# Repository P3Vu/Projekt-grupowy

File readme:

Repozytorium powstało na potrzeby projektu grupowego (Edycja 2020/2021) prowadzonego jako jedne z wymagań na II stopniu studiów 
kierunku Elektronika i Telekomunikacja.

Tematem projektu opisanego w repozytorium jest Rozproszony System Inteligentnego Oświetlenia Ulicznego, którego celem jest
stworzenie systemu składającego się z lamp ulicznych dokonujących odpowiednich pomiarów oraz komunikujących się bezprzewodowo
(np. z wykorzystaniem interfejsu LoRaWAN) z serwerem celem sterowania oraz zarządzania.

Członkami zespołu są studenci katedry Metrologii i Optoelektroniki z specjalizacją uzupełniająca Systemy Wbudowane:

1. inż. Paweł Wojciechowski (Lider Zespołu)
2. inż. Luiza Błaszczak
3. inż. Anita Kaszuba

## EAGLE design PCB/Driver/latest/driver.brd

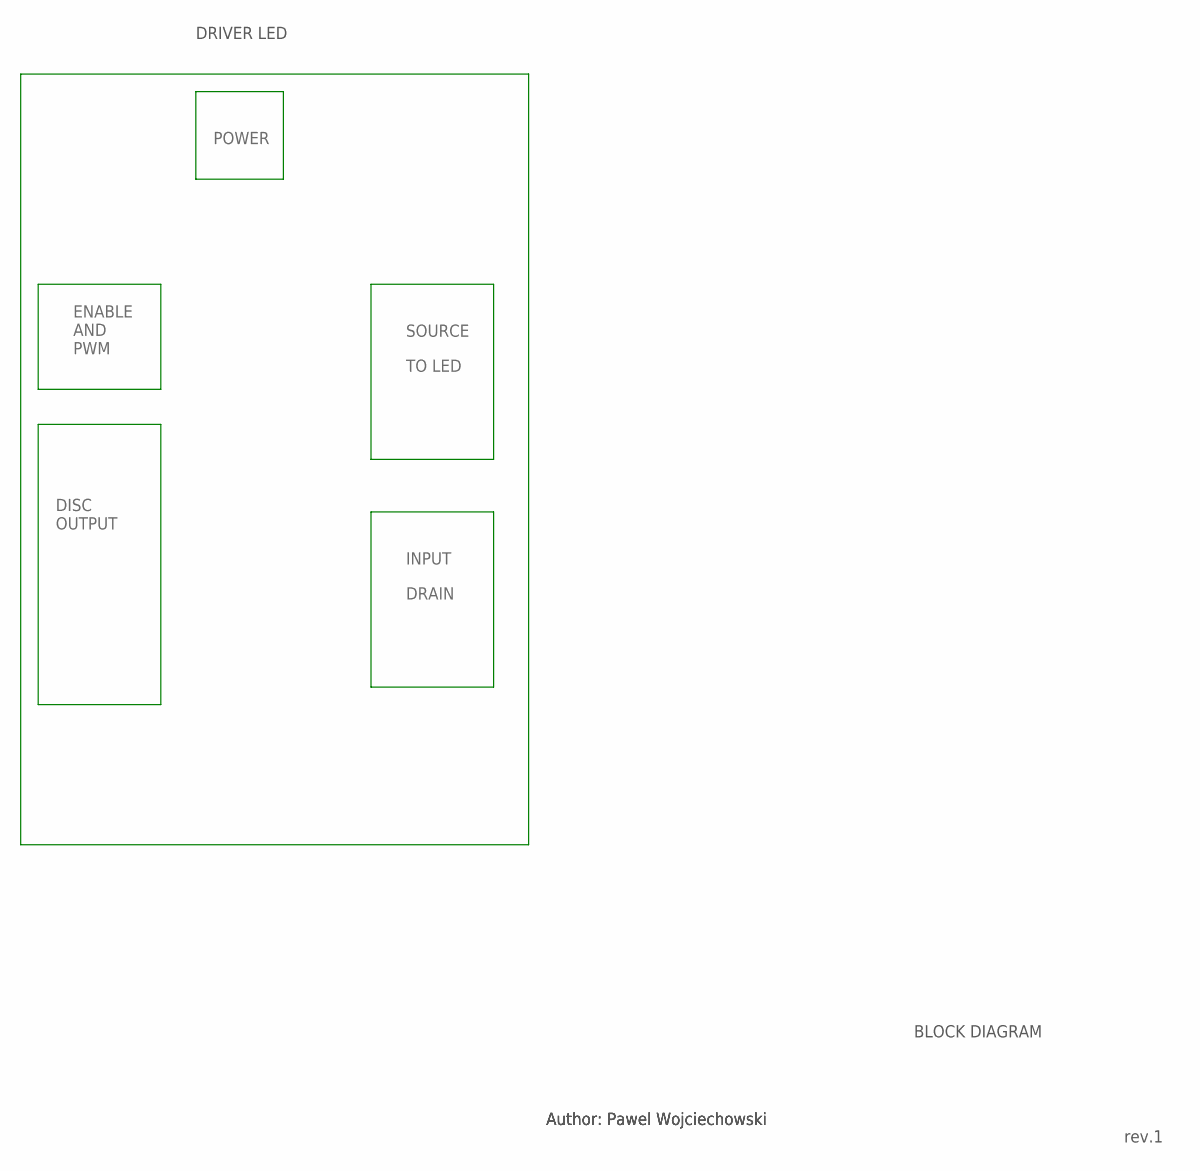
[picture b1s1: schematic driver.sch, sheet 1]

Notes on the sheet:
BLOCK DIAGRAM
Author: Pawel Wojciechowski
DRIVER LED
rev.1
ENABLE AND PWM
DISC OUTPUT
POWER
SOURCE
TO LED
INPUT
DRAIN

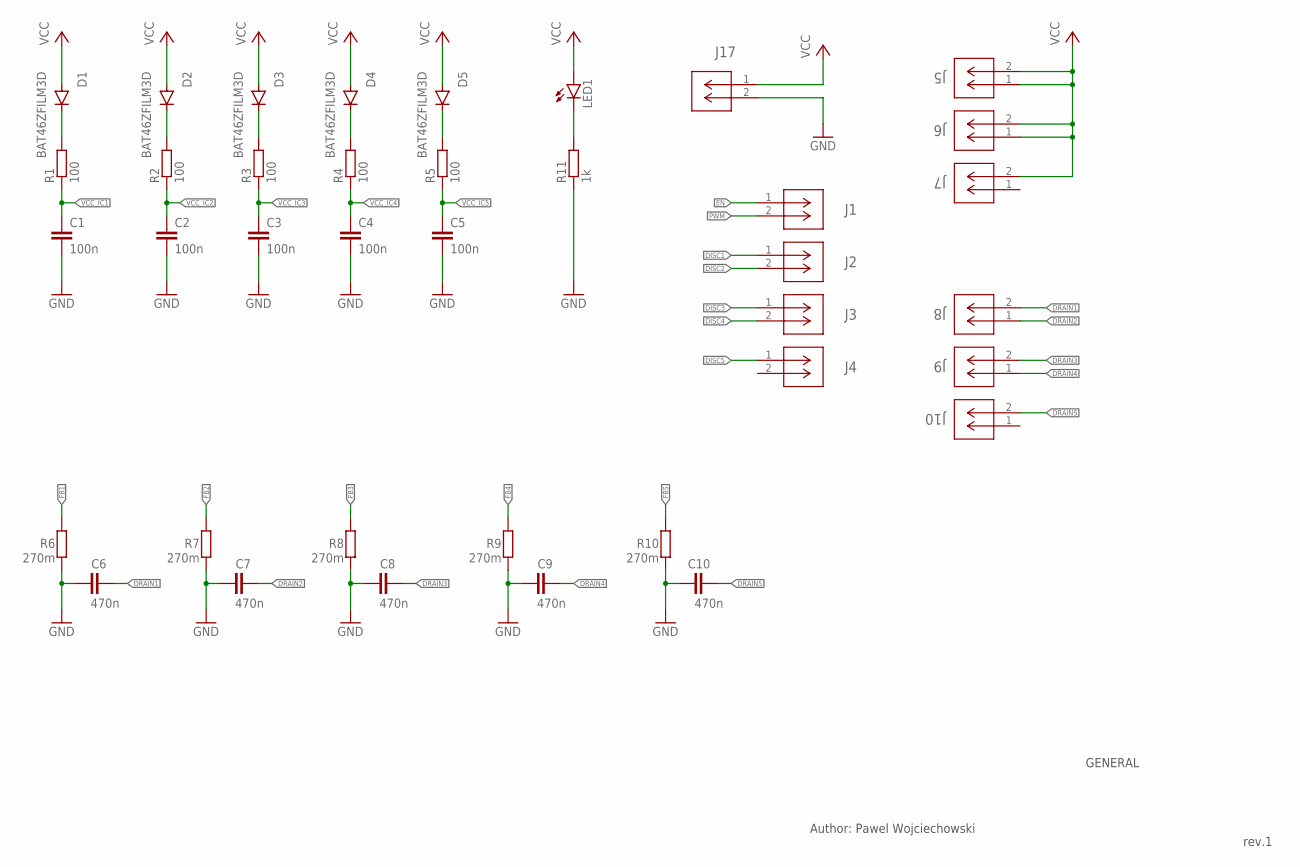
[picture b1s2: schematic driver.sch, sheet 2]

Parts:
C1, C2, C3, C4, C5: 100n; C0603
C6, C7, C8, C9, C10: 470n; C0805
D1, D2, D3, D4, D5: BAT46ZFILM3D; SOD-123
J1, J2, J3, J4, J5, J6, J7, J8, J9, J10, J17: 1776275-2; CONN2_1776275-2
LED1: LEDSMT1206; 1206
R1, R2, R3, R4, R5: 100; R0603
R6, R7, R8, R9, R10: 270m; R0603
R11: 1k; R0603

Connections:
DISC1: J2.1; also elsewhere on the board
DISC2: J2.2; also elsewhere on the board
DISC3: J3.1; also elsewhere on the board
DISC4: J3.2; also elsewhere on the board
DISC5: J4.1; also elsewhere on the board
DRAIN1: C6.2, J8.2; also elsewhere on the board
DRAIN2: C7.2, J8.1; also elsewhere on the board
DRAIN3: C8.2, J9.2; also elsewhere on the board
DRAIN4: C9.2, J9.1; also elsewhere on the board
DRAIN5: C10.2, J10.2; also elsewhere on the board
EN: J1.1; also elsewhere on the board
FB1: R6.2; also elsewhere on the board
FB2: R7.2; also elsewhere on the board
FB3: R8.2; also elsewhere on the board
FB4: R9.2; also elsewhere on the board
FB5: R10.2; also elsewhere on the board
GND: C1.2, C2.2, C3.2, C4.2, C5.2, C6.1, C7.1, C8.1, C9.1, C10.1, J17.2, R6.1, R7.1, R8.1, R9.1, R10.1, R11.1; also elsewhere on the board
unnamed: D1.C, R1.2
unnamed: D2.C, R2.2
unnamed: D3.C, R3.2
unnamed: D4.C, R4.2
unnamed: D5.C, R5.2
unnamed: LED1.C, R11.2
PWM: J1.2; also elsewhere on the board
VCC: D1.A, D2.A, D3.A, D4.A, D5.A, J5.1, J5.2, J6.1, J6.2, J7.2, J17.1, LED1.A
VCC_IC1: C1.1, R1.1; also elsewhere on the board
VCC_IC2: C2.1, R2.1; also elsewhere on the board
VCC_IC3: C3.1, R3.1; also elsewhere on the board
VCC_IC4: C4.1, R4.1; also elsewhere on the board
VCC_IC5: C5.1, R5.1; also elsewhere on the board

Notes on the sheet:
Author: Pawel Wojciechowski
rev.1
GENERAL

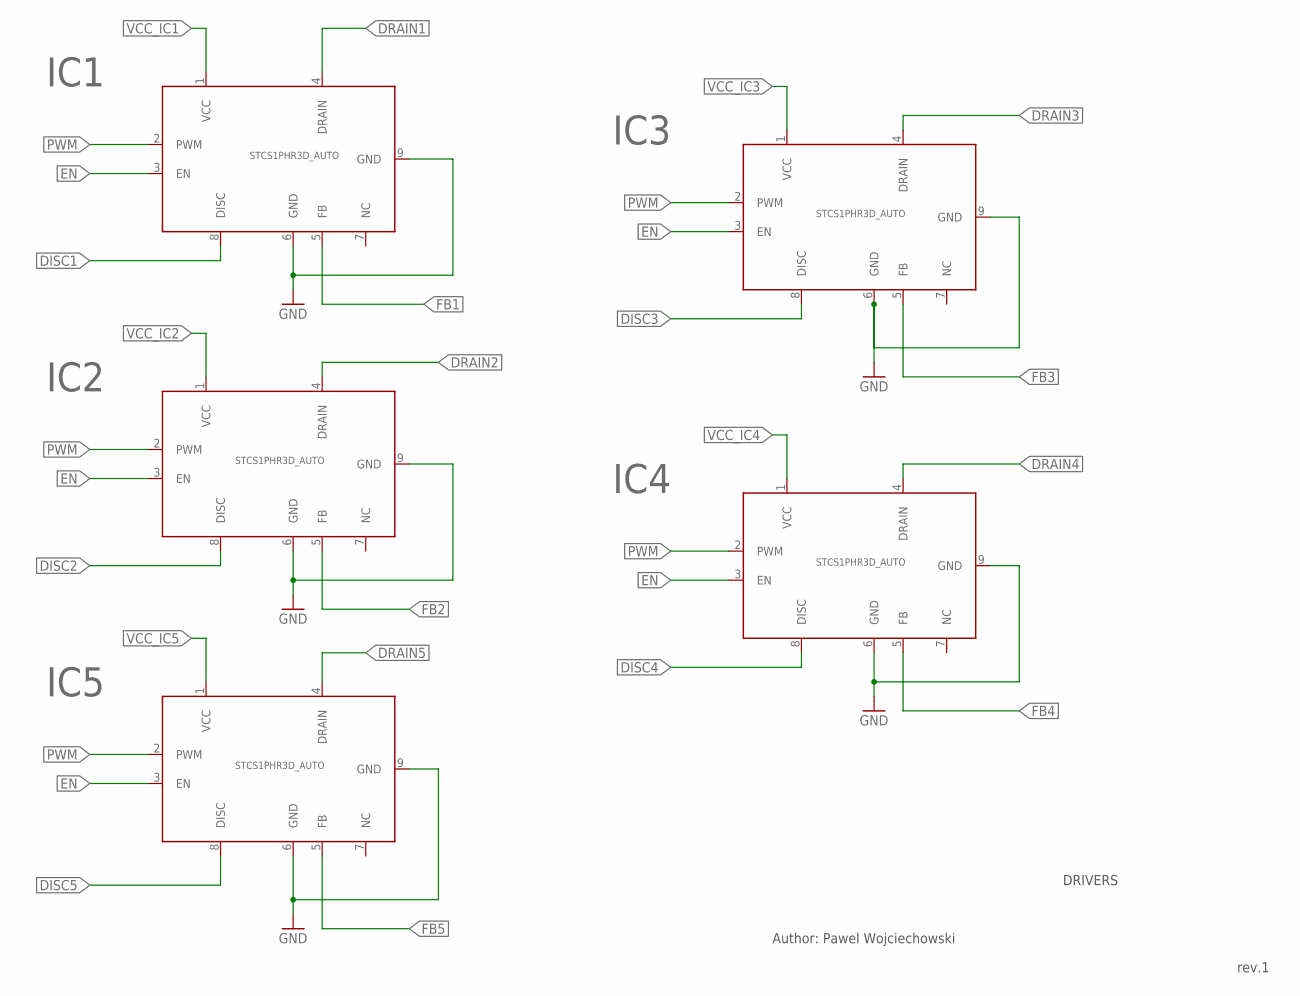
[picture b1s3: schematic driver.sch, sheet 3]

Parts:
IC1, IC2, IC3, IC4, IC5: STCS1PHR3D_AUTO; SOIC127P600X170-9T251X320N

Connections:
DISC1: IC1.8 (DISC); also elsewhere on the board
DISC2: IC2.8 (DISC); also elsewhere on the board
DISC3: IC3.8 (DISC); also elsewhere on the board
DISC4: IC4.8 (DISC); also elsewhere on the board
DISC5: IC5.8 (DISC); also elsewhere on the board
DRAIN1: IC1.4 (DRAIN); also elsewhere on the board
DRAIN2: IC2.4 (DRAIN); also elsewhere on the board
DRAIN3: IC3.4 (DRAIN); also elsewhere on the board
DRAIN4: IC4.4 (DRAIN); also elsewhere on the board
DRAIN5: IC5.4 (DRAIN); also elsewhere on the board
EN: IC1.3 (EN), IC2.3 (EN), IC3.3 (EN), IC4.3 (EN), IC5.3 (EN); also elsewhere on the board
FB1: IC1.5 (FB); also elsewhere on the board
FB2: IC2.5 (FB); also elsewhere on the board
FB3: IC3.5 (FB); also elsewhere on the board
FB4: IC4.5 (FB); also elsewhere on the board
FB5: IC5.5 (FB); also elsewhere on the board
GND: IC1.6 (GND), IC1.9 (GND), IC2.6 (GND), IC2.9 (GND), IC3.6 (GND), IC3.9 (GND), IC4.6 (GND), IC4.9 (GND), IC5.6 (GND), IC5.9 (GND); also elsewhere on the board
PWM: IC1.2 (PWM), IC2.2 (PWM), IC3.2 (PWM), IC4.2 (PWM), IC5.2 (PWM); also elsewhere on the board
VCC_IC1: IC1.1 (VCC); also elsewhere on the board
VCC_IC2: IC2.1 (VCC); also elsewhere on the board
VCC_IC3: IC3.1 (VCC); also elsewhere on the board
VCC_IC4: IC4.1 (VCC); also elsewhere on the board
VCC_IC5: IC5.1 (VCC); also elsewhere on the board

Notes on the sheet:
DRIVERS
Author: Pawel Wojciechowski
rev.1

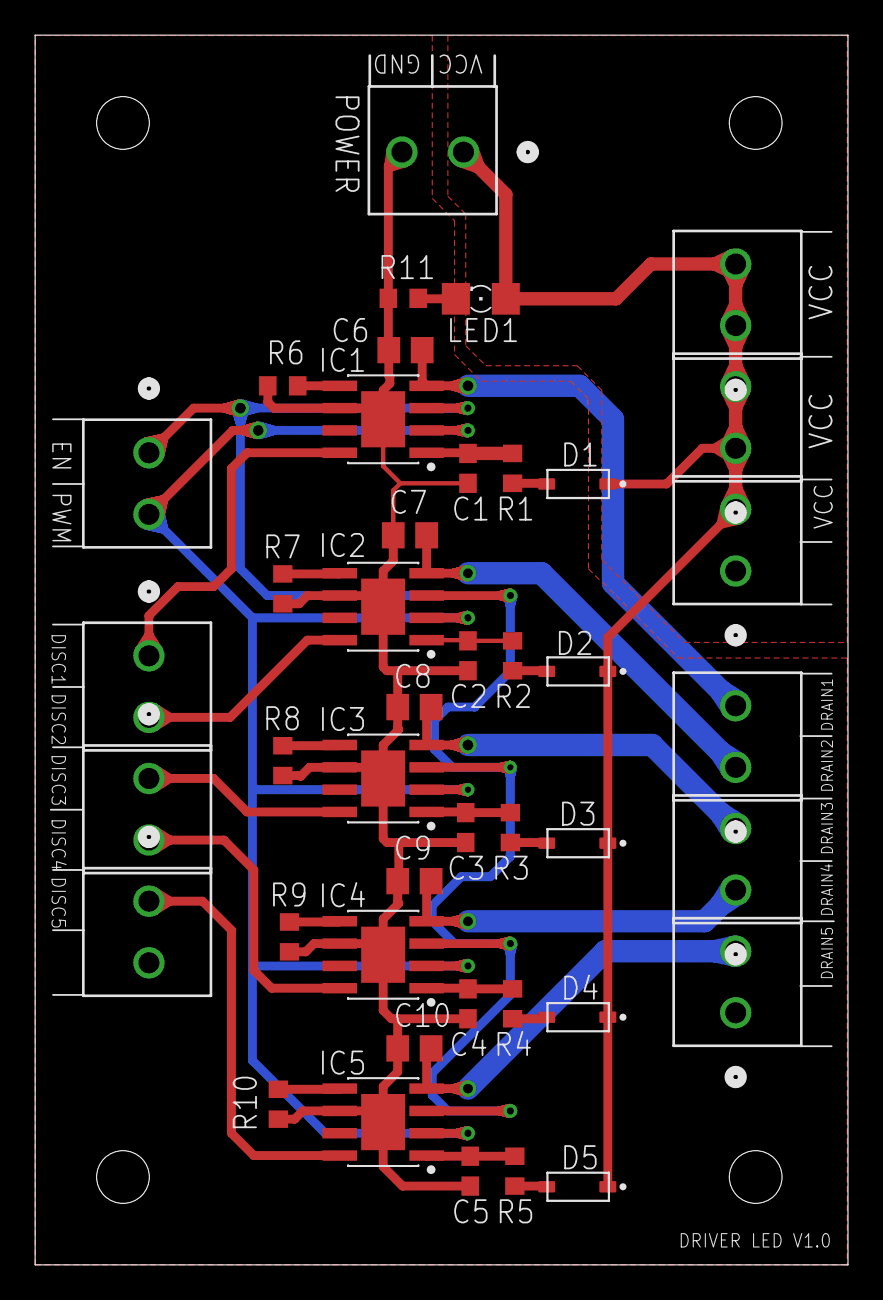
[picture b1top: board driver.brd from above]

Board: 2 copper layers, 46.3 x 70.0 mm, 43 parts (0 on the bottom side), 30 nets.

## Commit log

2020-04-09 Rename PMS.ioc to Czujnik Pylu/ PMS.ioc
    Przenosze do odpowiedniego folderu
2020-04-09 Rename Czujnik Pylu/ PMS.ioc to Czujnik pylu/PMS.ioc
2020-04-09 Rename Inc/main.h to Czujnik pylu/Inc/main.h
2020-04-09 Create Czujnik pylu
2020-05-04 Test dodawania test.c
2020-05-04 Usuwam test.c
2020-05-04 Dodaje pelny projekt z czujnikiem pylu PMS3003
2020-05-04 Usuwam poprzedni niepelny folder z czujnikiem pylu
2020-05-04 Projekt PCB
2020-05-07 Test
2020-05-08 Added Czujnik BME280
2020-05-08 Modernizacja repozytorium
2020-05-08 Modernizacja struktury repozytorium
2020-07-03 Zalozenie projektu w Eagle oraz dodanie schematu blokowego
2020-07-03 Poprawienie schematu blokowego
2020-07-04 Kosmetyczne poprawki
2020-07-04 Dodanie plikow w PMS wskazanych przez gita jako nowe
2020-07-26 Projekt drivera do LED
2020-08-09 Komunikacja za pomoca CC2530
2020-08-09 CC2530
2020-09-01 Driver LED
2020-09-18 dziala zigbee po obu stronach (nadawianie i odbior)

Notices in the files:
parts and their libraries:
COPYRIGHT: Copyright (C) 2016 Accelerated Designs. All rights reserved
